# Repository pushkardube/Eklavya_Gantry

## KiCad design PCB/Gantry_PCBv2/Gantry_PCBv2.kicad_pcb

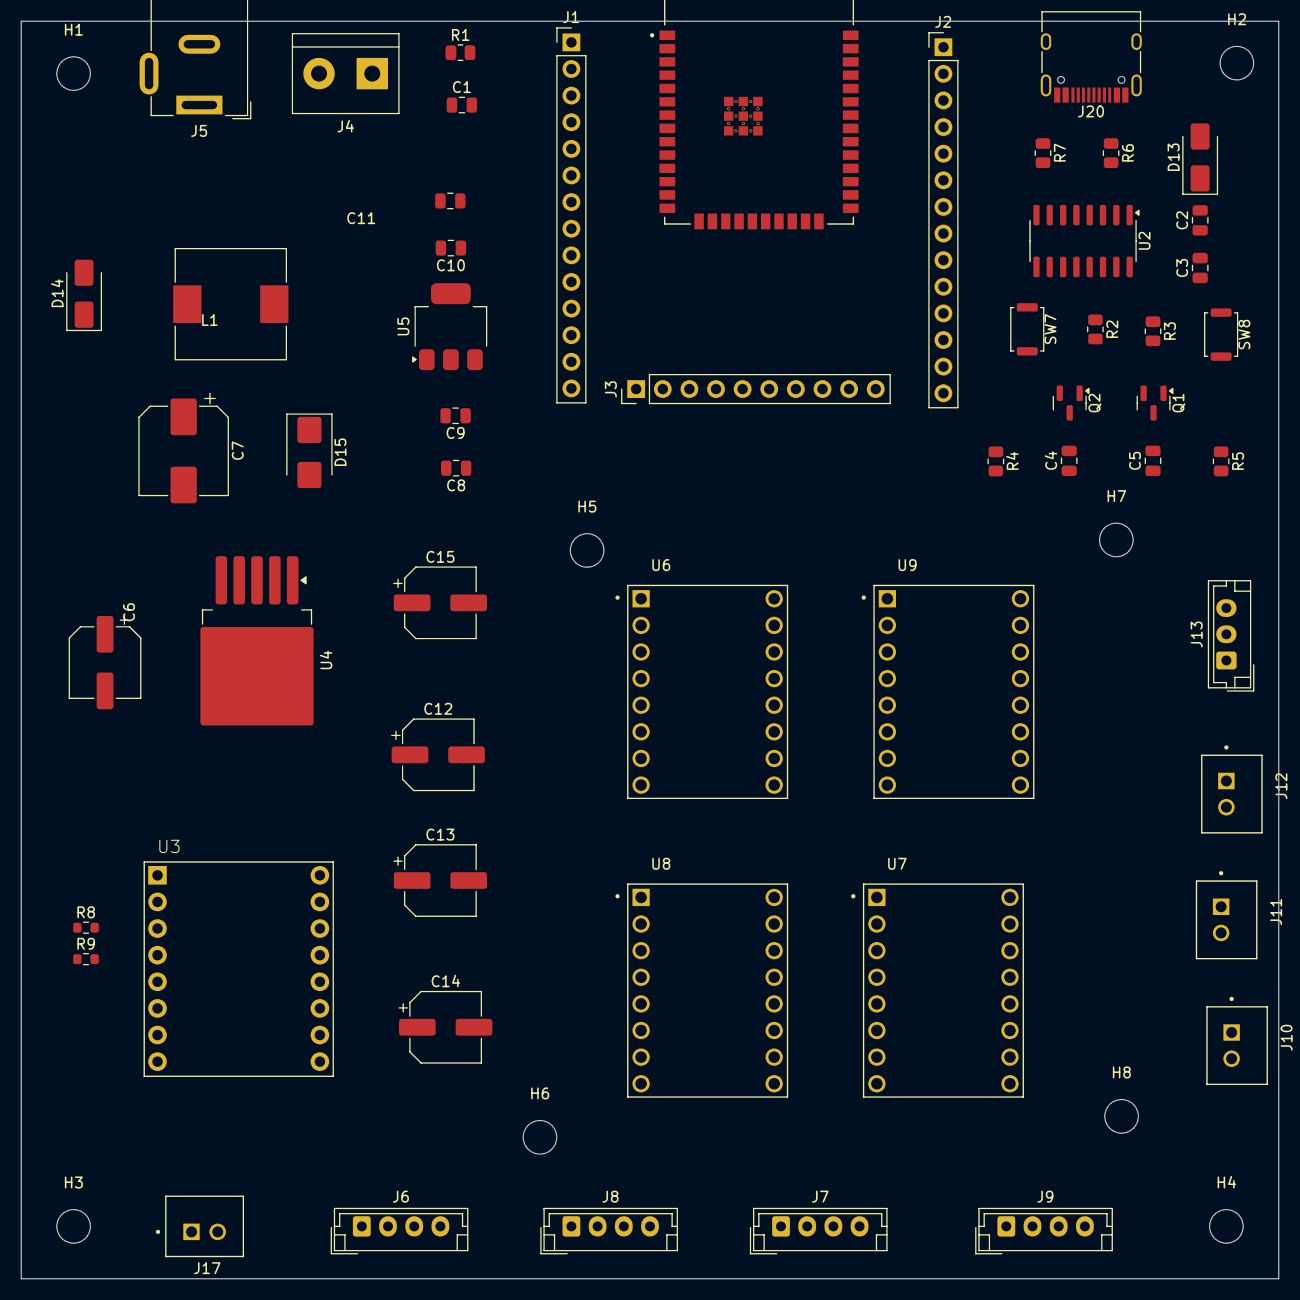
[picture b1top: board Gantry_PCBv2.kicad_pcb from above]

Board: 2 copper layers, 120.0 x 120.0 mm, 64 parts (0 on the bottom side), 60 nets.

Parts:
C1, C2, C3, C4, C5, C9, C10: 0.1uF; C_0805_2012Metric
C6: 100uF; CP_Elec_6.3x7.7
C7: 470uF; CP_Elec_8x10
C8: 10uF; C_0805_2012Metric
C11: 22uF; C_0805_2012Metric
C12, C13, C14, C15: 100u; CP_Elec_6.3x7.7
D13: SS14; D_SMA
D14: SS24; D_SMA
D15: SS34; D_SMB
H1, H2, H3, H4, H5, H6, H7, H8: MountingHole; MountingHole_3.2mm_M3
J1, J2: Conn_01x14; PinHeader_1x14_P2.54mm_Vertical
J3: Conn_01x10; PinHeader_1x10_P2.54mm_Vertical
J4: Screw_Terminal_01x02; TerminalBlock_bornier-2_P5.08mm
J5: DCJ200-10-A-XX-X_REVA; BarrelJack_Wuerth_6941xx301002
J6, J7, J8, J9: Conn_01x04_Pin; JST_EH_B4B-EH-A_1x04_P2.50mm_Vertical
J10, J11, J12, J17: B2B-XH-A_LF__SN_; JST_B2B-XH-A_LF__SN_
J13: Conn_01x03_Pin; JST_EH_B3B-EH-A_1x03_P2.50mm_Vertical
J20: TYPE-C-31-M-12; USB_C_Receptacle_HRO_TYPE-C-31-M-12
L1: 100uH; L_10.4x10.4_H4.8
Q1, Q2: SS8050; SOT-23
R1, R2, R3, R4, R5: 10K; R_0805_2012Metric
R6, R7: 5.1K; R_0805_2012Metric
R8, R9: 1k; R_0603_1608Metric
SW7: SW_0; SW_Push_SPST_NO_Alps_SKRK
SW8: SW_EN; SW_Push_SPST_NO_Alps_SKRK
U1: ESP32-WROOM-32E; XCVR_ESP32-WROOM-32E__4MB_HIGH_TEMP_
U2: CH340C; SOIC-16_3.9x9.9mm_P1.27mm
U3: TB6612FNG H-bridge Motor Driver; TB6612FNG
U4: LM2576S-5; TO-263-5_TabPin3
U5: AMS1117-3.3; SOT-223-3_TabPin2
U6, U7, U8, U9: DRV8825_STEPPER_MOTOR_DRIVER_CARRIER; IC_DRV8825_STEPPER_MOTOR_DRIVER_CARRIER

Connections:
/0: C4.2, J2.14, Q2.3, R4.1, SW7.2, U1.25 (IO0)
/2: J3.10, U1.24 (IO2)
/3V3: C2.1, C10.1, C11.1, J1.2, R1.2, R4.2, R5.2, U1.2 (VDD), U2.16 (VCC), U5.2 (VO), U6.2 (M0), U6.3 (M1), U6.4 (M2), U6.5 (~RST), U6.6 (~SLP), U7.2 (M0), U7.3 (M1), U7.4 (M2), U7.5 (~RST), U7.6 (~SLP), U8.2 (M0), U8.3 (M1), U8.4 (M2), U8.5 (~RST), U8.6 (~SLP), U9.2 (M0), U9.3 (M1), U9.4 (M2), U9.5 (~RST), U9.6 (~SLP)
/4: J2.13, U1.26 (IO4)
/5: J2.10, U1.29 (IO5)
/5V: C7.1, L1.2, U4.4 (FB)
/5V_P: C8.1, C9.1, D13.1 (K), U5.3 (VI)
/12: J1.14, U1.14 (IO12), U9.7 (STEP)
/12V: D14.2 (A), J4.2, J5.1
/12V_P: C12.1, C13.1, C14.1, C15.1, J13.2, U6.16 (VMOT), U7.16 (VMOT), U8.16 (VMOT), U9.16 (VMOT)
/13: J3.2, R9.1, U1.16 (IO13)
/14: J1.13, U1.13 (IO14), U9.8 (DIR)
/15: J3.9, J10.1, U1.23 (IO15)
/16: J2.12, U1.27 (IO16)
/17: J2.11, U1.28 (IO17)
/18: J2.9, J12.1, R8.1, U1.30 (IO18)
/19: J2.8, J11.1, U1.31 (IO19)
/21: J2.6, U1.33 (IO21)
/22: J2.3, U1.36 (IO22), U6.8 (DIR)
/23: J2.2, U1.37 (IO23), U6.7 (STEP)
/25: J1.10, U1.10 (IO25), U7.8 (DIR), U8.8 (DIR)
/26: J1.11, U1.11 (IO26), U7.7 (STEP), U8.7 (STEP)
/27: J1.12, U1.12 (IO27)
/32: J1.8, U1.8 (IO32)
/33: J1.9, U1.9 (IO33)
/34: J1.6, U1.6 (IO34)
/35: J1.7, U1.7 (IO35)
/36: J1.4, U1.4 (SENSOR_VP)
/39: J1.5, U1.5 (SENSOR_VN)
/CC1: J20.A5 (CC1), R6.1
/CC2: J20.B5 (CC2), R7.1
/DN1: J20.A7 (DN1), J20.B7 (DN2), U2.6 (UD-)
/DP1: J20.A6 (DP1), J20.B6 (DP2), U2.5 (UD+)
/EN: C1.1, C5.2, J1.3, Q1.3, R1.1, R5.1, SW8.2, U1.3 (EN)
/RXD: J2.5, U1.34 (RXD0/IO3), U2.2 (TXD)
/SM1_A1: J9.1, U9.12 (A1)
/SM1_A2: J9.2, U9.11 (A2)
/SM1_B1: J9.3, U9.13 (B1)
/SM1_B2: J9.4, U9.14 (B2)
/SM2_A1: J6.1, U6.12 (A1)
/SM2_A2: J6.2, U6.11 (A2)
/SM2_B1: J6.3, U6.13 (B1)
/SM2_B2: J6.4, U6.14 (B2)
/SM3_A1: J7.1, U7.12 (A1)
/SM3_A2: J7.2, U7.11 (A2)
/SM3_B1: J7.3, U7.13 (B1)
/SM3_B2: J7.4, U7.14 (B2)
/SM4_A1: J8.1, U8.12 (A1)
/SM4_A2: J8.2, U8.11 (A2)
/SM4_B1: J8.3, U8.13 (B1)
/SM4_B2: J8.4, U8.14 (B2)
/TXD: J2.4, U1.35 (TXD0/IO1), U2.3 (RXD)
/~DTR: Q2.2, R2.1, U2.13 (~DTR)
/~RTS: Q1.2, R3.1, U2.14 (~RTS)
GND: C1.2, C2.2, C3.2, C4.1, C5.1, C6.2, C7.2, C8.2, C9.2, C10.2, C11.2, C12.2, C13.2, C14.2, C15.2, D15.2 (A), J1.1, J2.1, J3.1, J4.1, J5.2, J5.3, J10.2, J11.2, J12.2, J13.3, J20.S1 (SHIELD), R6.2, R7.2, SW7.1, SW8.1, U1.1 (GND), U1.15 (GND), U1.38 (GND), U2.1 (GND), U4.3 (GND), U4.5 (~ON/OFF), U5.1 (GND), U6.1 (~EN), U6.9 (GND), U6.15 (GND_MOT), U7.1 (~EN), U7.9 (GND), U7.15 (GND_MOT), U8.1 (~EN), U8.9 (GND), U8.15 (GND_MOT), U9.1 (~EN), U9.9 (GND), U9.15 (GND_MOT)
unnamed: C6.1, D14.1 (K), U4.1 (VIN)
unnamed: D15.1 (K), L1.1, U4.2 (OUT)
unnamed: Q1.1, R2.2
unnamed: Q2.1, R3.2
unnamed: C3.1, U2.4 (V3)

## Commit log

2025-12-27 Changes in PCB
2025-12-28 Component Placement done
